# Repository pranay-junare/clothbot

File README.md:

# Cloth Manipulation using Self-supervised value network
	
[comment]: <>  (## _The Last Markdown Editor, Ever_)

<!--  -->

## Demo

Video Link: [Demo](https://youtu.be/vcyFeuL4r6w?si=Km419zFCMDmrSFIV)

Rollout on rectangular cloth 1            |  Rollout on rectangular cloth 2
:-------------------------:|:-------------------------:
  |  

Rollout on unseen tshirt 1            |  Rollout on unseen tshirt 2
:-------------------------:|:-------------------------:
  |  

## Abstract
Cloth manipulation is a challenging problem due to cloth’s complex dynamics, almost infinite DoF and severe self-occlusion. Moreover, most cloth manipulation tasks require chaining of multiple action primitives such pick, place, drag fling, stretch, etc. In addition, most of the current cloth manipulation research only use quasi-static actions taking large amount of time to manipulate different garments. Thus our project aims to tackle this complex manipulation problem by imparting the capability of dynamic cloth unfolding to a bimanual robot using a high- velocity dynamic fling action. We focus particularly on the task of cloth unfolding, a typical first step in most cloth manipulation tasks. We trained our self-supervised Value network policy based on Spatial Action Maps. The policy is completely trained on only rectangular cloths in simulation. We have leveraged Softgym simulator and have trained the policy for 7 days until convergence. The policy achieves a cloth unfolding mean coverage of 95.09% over 200 rollouts on rectangular cloths. Interestingly our policy also generalizes to unseen cloths such as T-shirts while achieving the mean coverage of 87.68%. It also transfers to the real-world cloths in a zero-shot manner without any need of fine-tuning. Real-world results are evaluated on a UR5e dual-arm robot.     

## Poster

### Acknowledgement

+ This work is the re-implementation of the below paper, so if you find it useful please cite the Flingbot paper: 
    + "Flingbot: The unreasonable effectiveness of dynamic manipulation for cloth unfolding.", Ha, Huy, and Shuran Song, In Conference on Robot Learning, pp. 24-33. PMLR, 2022.

+ Other References:
    + “Unfolding the literature: A review of robotic cloth manipulation.”, Longhini, Alberta et al, Annual Review of Control, Robotics, and Autonomous Systems 8, 2024. 
    + "Speedfolding: Learning efficient bimanual folding of garments.", Avigal, Yahav, Lars Berscheid, Tamim Asfour, Torsten Kröger, and Ken Goldberg, In 2022 IEEE/RSJ International Conference on Intelligent Robots and Systems (IROS), pp. 1-8. IEEE, 2022.
    + “Softgym: Benchmarking deep reinforcement learning for deformable object manipulation”,Xingyu Lin, Yufei Wang, Jake Olkin, and David Held, Conference on Robot Learning, 2020. 
    + “Learning particle dynamics for manipulating rigid bodies, deformable objects, and fluids.”, Li, Y., Wu, J., Tedrake, R., Tenenbaum, J., & Torralba, A. (2018). arXiv:1810.01566

### License

MIT

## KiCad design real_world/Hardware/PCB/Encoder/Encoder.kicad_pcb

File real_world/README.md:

# For final dual-arm UR5 control movements

- mamba activate teleop
- python real_world/TeleopMethods/launch.py
- python real_world/TeleopMethods/main.py

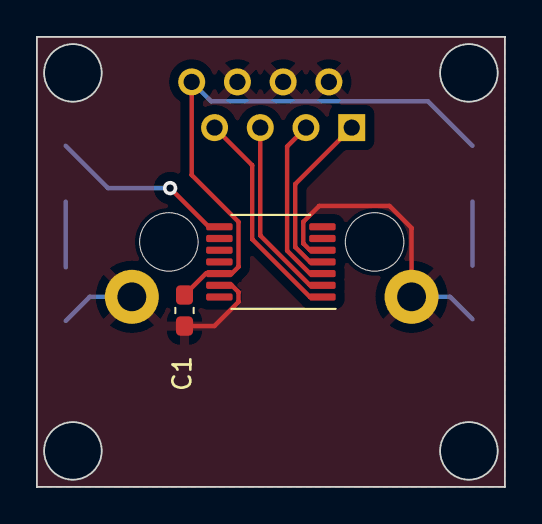
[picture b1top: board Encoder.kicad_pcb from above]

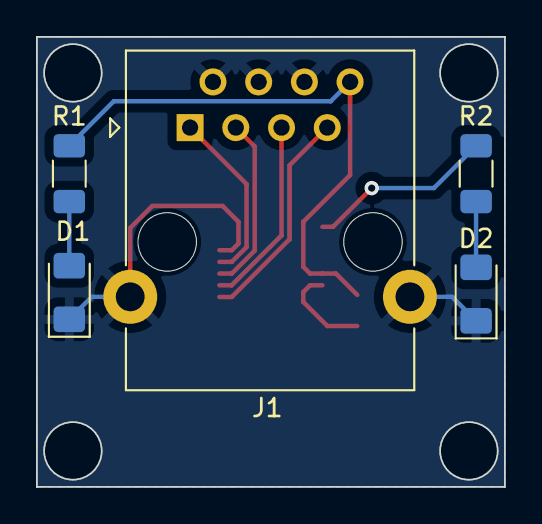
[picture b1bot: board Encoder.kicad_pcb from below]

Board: 2 copper layers, 26.0 x 25.0 mm, 7 parts (5 on the bottom side), 9 nets.

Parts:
C1: 1000nF; C_0603_1608Metric_Pad1.08x0.95mm_HandSolder
D1: Red; LED_1206_3216Metric_Pad1.42x1.75mm_HandSolder
D2: LED; LED_1206_3216Metric_Pad1.42x1.75mm_HandSolder
J1: RJ45_Shielded; RJ45_Ninigi_GE
R1, R2: 65; R_1206_3216Metric_Pad1.30x1.75mm_HandSolder
U1: AS5047D; TSSOP-14_4.4x5mm_P0.65mm

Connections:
+3.3V: C1.1, J1.8, R1.2, U1.12 (VDD3V3)
CLK: J1.5, U1.2 (CLK)
CS: J1.7, U1.1 (~CS)
GND: C1.2, D1.1 (K), D2.1 (K), J1.2, J1.4, J1.6, J1.SH, U1.5 (TST), U1.13 (GND)
MISO: J1.3, U1.3 (MISO)
MOSI: J1.1, U1.4 (MOSI)
unnamed: D1.2 (A), R1.1
unnamed: D2.2 (A), R2.1
unnamed: R2.2, U1.8 (W/PWM)

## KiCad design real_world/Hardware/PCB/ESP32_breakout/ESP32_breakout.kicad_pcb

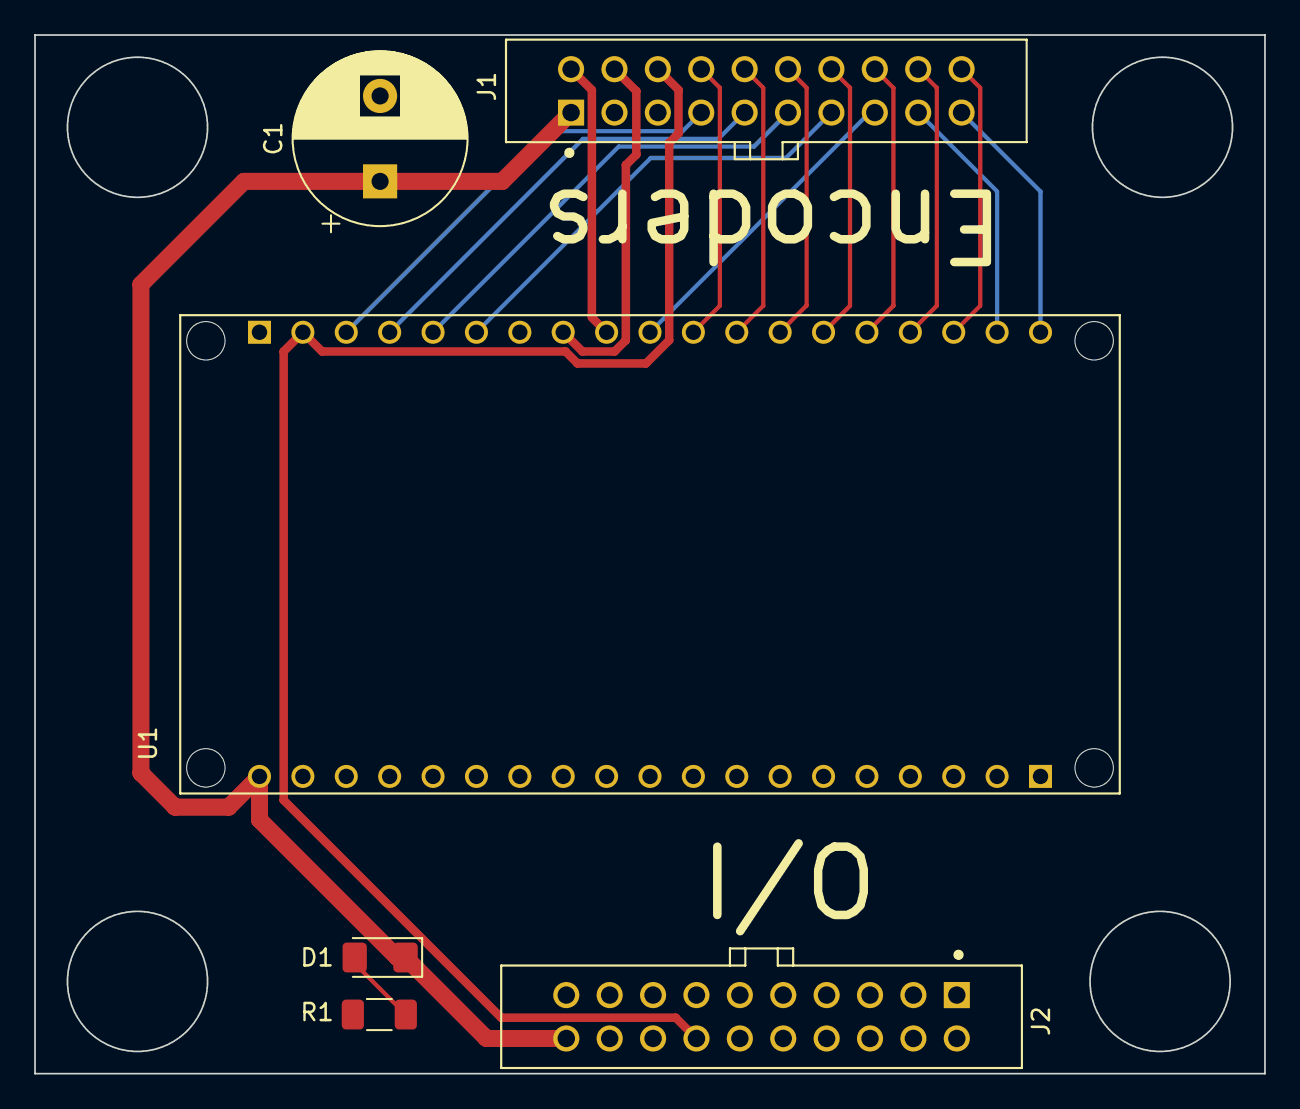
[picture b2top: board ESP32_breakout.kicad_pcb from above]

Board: 2 copper layers, 72.0 x 60.8 mm, 6 parts (0 on the bottom side), 20 nets.

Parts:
C1: C_Polarized; CP_Radial_D10.0mm_P5.00mm
D1: LED; D_1206_3216Metric_Pad1.42x1.75mm_HandSolder
J1: Encoder; SULLINS_SFH11-PBPC-D10-ST-BK
J2: IO; SULLINS_SFH11-PBPC-D10-ST-BK
R1: 150; R_1206_3216Metric_Pad1.30x1.75mm_HandSolder
U1: ESP32_NODEMCU; MODULE_ESP32_NODEMCU

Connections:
+3.3V: C1.1, D1.1 (K), J1.1, J2.20, U1.J5_19 (3V3)
CLK: J1.2, J2.10, U1.J4_9 (G18)
CS0_L: J1.20, U1.J4_17 (SD1)
CS0_R: J1.7, U1.J4_3 (G22)
CS1_L: J1.18, U1.J4_16 (G15)
CS1_R: J1.9, U1.J4_4 (TXD)
CS2_L: J1.16, U1.J4_15 (G2)
CS2_R: J1.11, U1.J4_5 (RXD)
CS3_L: J1.14, U1.J4_14 (G0)
CS3_R: J1.13, U1.J4_6 (G21)
CS4_L: J1.12, U1.J4_13 (G4)
CS4_R: J1.15, U1.J4_10 (G5)
CS5_L: J1.10, U1.J4_12 (G16)
CS5_R: J1.17, U1.J4_18 (SD0)
CS6_L: J1.8, U1.J4_11 (G17)
CS6_R: J1.19, U1.J4_19 (CLK)
GND: C1.2, J1.3, J1.5, J2.16, J2.18, R1.1, U1.J4_1 (GND_J4_1), U1.J4_7 (GND_J4_7), U1.J5_6 (GND_J5_6)
MISO: J1.4, J2.12, U1.J4_8 (G19)
MOSI: J1.6, J2.14, U1.J4_2 (G23)
unnamed: D1.2 (A), R1.2

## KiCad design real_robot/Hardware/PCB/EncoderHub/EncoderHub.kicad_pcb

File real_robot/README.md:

# Spark Expert Demonstration Platform

TODO

mamba activate teleop
python launch.py
git -c user.name="Pranay Junare" -c user.email="junarepranay@gmail.com" commit -m "UR5 setup"

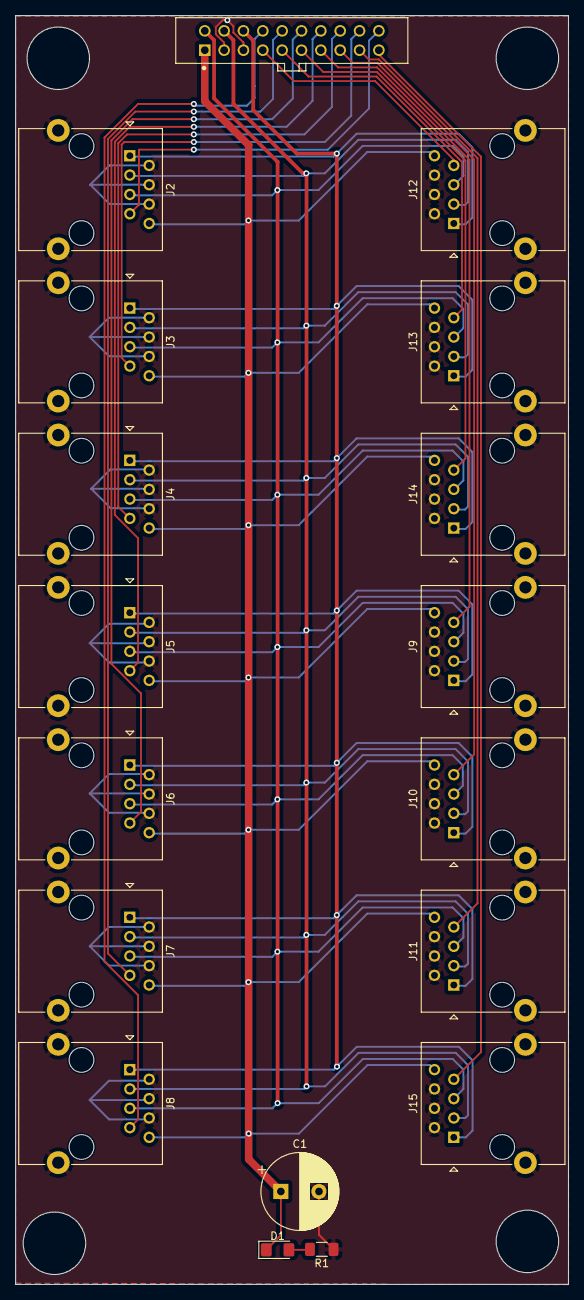
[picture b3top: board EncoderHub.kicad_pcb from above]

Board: 2 copper layers, 72.6 x 166.6 mm, 18 parts (0 on the bottom side), 20 nets.

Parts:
C1: C_Polarized; CP_Radial_D10.0mm_P5.00mm
D1: LED; D_1206_3216Metric_Pad1.42x1.75mm_HandSolder
J1: SFH11-PBPC-D10-ST-BK; SULLINS_SFH11-PBPC-D10-ST-BK
J2: Encoder0_L; RJ45_Ninigi_GE
J3: Encoder1_L; RJ45_Ninigi_GE
J4: Encoder2_L; RJ45_Ninigi_GE
J5: Encoder3_L; RJ45_Ninigi_GE
J6: Encoder4_L; RJ45_Ninigi_GE
J7: Encoder5_L; RJ45_Ninigi_GE
J8: Encoder6_L; RJ45_Ninigi_GE
J9: Encoder3_R; RJ45_Ninigi_GE
J10: Encoder4_R; RJ45_Ninigi_GE
J11: Encoder5_R; RJ45_Ninigi_GE
J12: Encoder0_R; RJ45_Ninigi_GE
J13: Encoder1_R; RJ45_Ninigi_GE
J14: Encoder2_R; RJ45_Ninigi_GE
J15: Encoder6_R; RJ45_Ninigi_GE
R1: 150; R_1206_3216Metric_Pad1.30x1.75mm_HandSolder

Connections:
+3.3V: C1.1, D1.1 (K), J1.1, J2.8, J3.8, J4.8, J5.8, J6.8, J7.8, J8.8, J9.8, J10.8, J11.8, J12.8, J13.8, J14.8, J15.8
CLK: J1.2, J2.5, J3.5, J4.5, J5.5, J6.5, J7.5, J8.5, J9.5, J10.5, J11.5, J12.5, J13.5, J14.5, J15.5
CS0_L: J1.20, J2.7
CS0_R: J1.7, J12.7
CS1_L: J1.18, J3.7
CS1_R: J1.9, J13.7
CS2_L: J1.16, J4.7
CS2_R: J1.11, J14.7
CS3_L: J1.14, J5.7
CS3_R: J1.13, J9.7
CS4_L: J1.12, J6.7
CS4_R: J1.15, J10.7
CS5_L: J1.10, J7.7
CS5_R: J1.17, J11.7
CS6_L: J1.8, J8.7
CS6_R: J1.19, J15.7
GND: C1.2, J1.3, J1.5, J2.2, J2.4, J2.6, J2.SH, J3.2, J3.4, J3.6, J3.SH, J4.2, J4.4, J4.6, J4.SH, J5.2, J5.4, J5.6, J5.SH, J6.2, J6.4, J6.6, J6.SH, J7.2, J7.4, J7.6, J7.SH, J8.2, J8.4, J8.6, J8.SH, J9.2, J9.4, J9.6, J9.SH, J10.2, J10.4, J10.6, J10.SH, J11.2, J11.4, J11.6, J11.SH, J12.2, J12.4, J12.6, J12.SH, J13.2, J13.4, J13.6, J13.SH, J14.2, J14.4, J14.6, J14.SH, J15.2, J15.4, J15.6, J15.SH, R1.1
MISO: J1.4, J2.3, J3.3, J4.3, J5.3, J6.3, J7.3, J8.3, J9.3, J10.3, J11.3, J12.3, J13.3, J14.3, J15.3
MOSI: J1.6, J2.1, J3.1, J4.1, J5.1, J6.1, J7.1, J8.1, J9.1, J10.1, J11.1, J12.1, J13.1, J14.1, J15.1
unnamed: D1.2 (A), R1.2

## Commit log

2024-11-21 base-code flingbot
2024-11-22 fixes to render evaluation
2024-11-22 task setup
2024-12-01 UR5 base code
2024-12-03 Added scripts to Move UR5 using MoveL
2024-12-04 Modified ur5_move.py
2024-12-05 Modified script to Control arm along every axis
2024-12-05 Modifed ur5_move.py
2024-12-05 Modified script to Grasp Cloth
2024-12-06 Added code to FLing
2024-12-07 Modified scripts to Run arms asynchronously
2024-12-08 Modified script to Grasp and Lift cloth
2024-12-08 camera setup and its debug
2024-12-08 camera debug refactor
2024-12-09 Modified script to Fling
2024-12-09 Added script for camera to world coordinates
2024-12-11 start training and sketch for inference
2024-12-11 Added scripts to perform Camera to world transformation
2024-12-12 Modified script for Coordinate Transformation
2024-12-12 Modified scripts
2024-12-13 Modified scripts to Transform COordinates
2024-12-15 Added Images
2024-12-30 real-world inference scripts
2025-01-17 updated readme with all details
2025-01-17 added unseen tshirt results
2025-01-17 fix typo
2025-01-17 Project Page template
2025-01-18 added clothbot content
2025-01-18 cleanup un-important
2025-01-24 added course number
